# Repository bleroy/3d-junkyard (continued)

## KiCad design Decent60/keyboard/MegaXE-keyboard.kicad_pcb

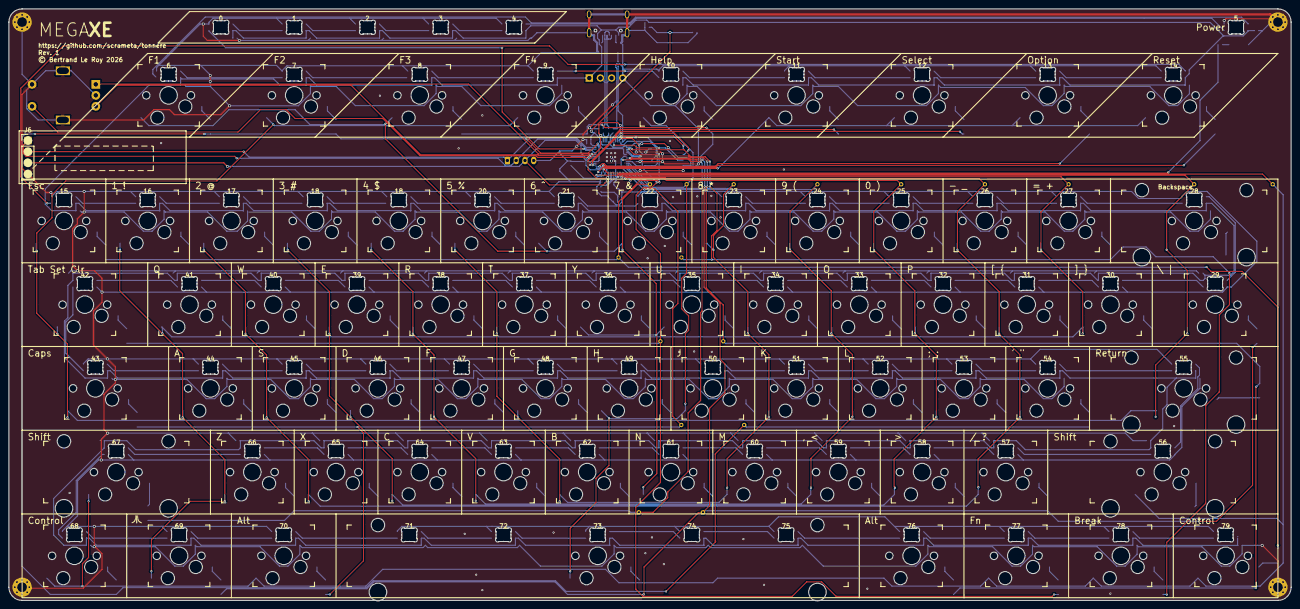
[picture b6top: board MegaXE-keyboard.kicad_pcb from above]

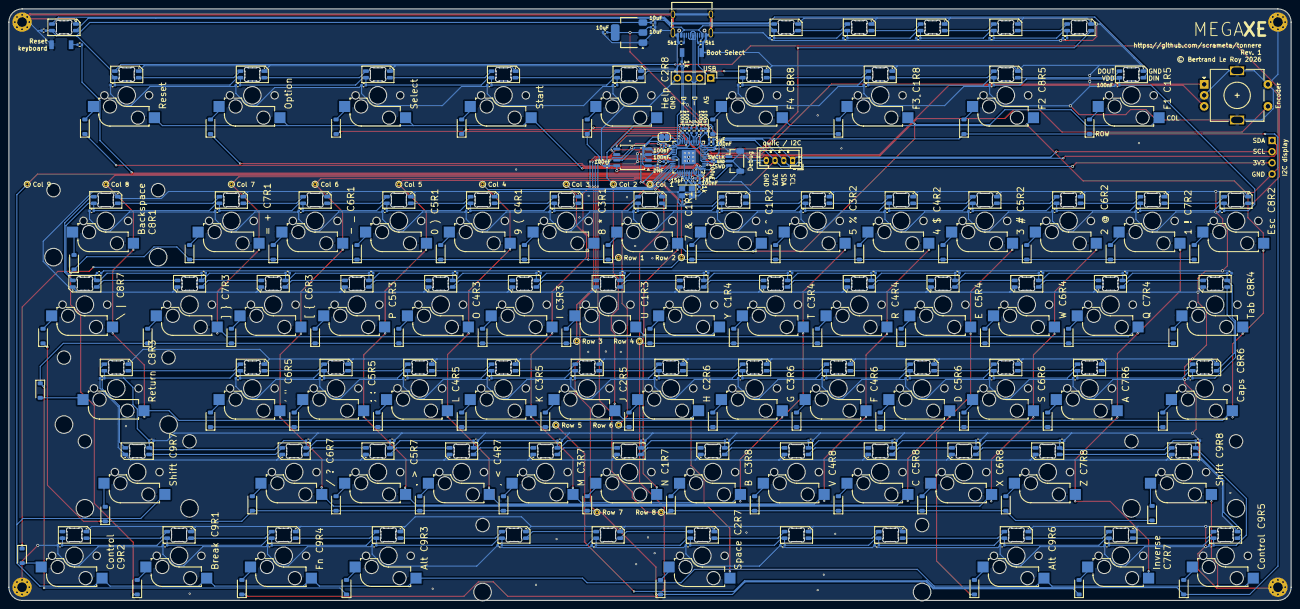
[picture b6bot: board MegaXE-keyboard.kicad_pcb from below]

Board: 2 copper layers, 291.8 x 134.6 mm, 359 parts (288 on the bottom side), 202 nets.

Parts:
C4, C6, C7, C8, C9, C10, C11, C12, C13, C42, C75, C76, C77, C78, C79, C80, C81, C82, C83, C84, C85, C86, C87, C88, C89, C90, C91, C92, C93, C94, C95, C96, C97, C98, C99, C100, C101, C102, C103, C104, C105, C106, C107, C108, C109, C110, C111, C112, C113, C114, C115, C116, C117, C118, C119, C120, C121, C123, C124, C125, C126, C127, C128, C129, C130, C131, C132, C133, C134, C135, C136, C137, C138, C139, C140, C141, C142, C143, C144, C145, C146, C147, C148, C149, C150, C151, C152, C153, C154, C155: 100nF; C_0402_1005Metric
C5, C14: 1uF; C_0402_1005Metric
C24, C25: 15pF; C_0402_1005Metric
C27, C28, C43: 10uF; C_0402_1005Metric
D17, D18, D19, D20, D21, D22, D23, D24, D25, D26, D27, D28, D29, D30, D31, D47, D49, D51, D53, D55, D57, D59, D61, D63, D65, D67, D69, D71, D73, D75, D77, D79, D81, D83, D85, D87, D89, D91, D93, D95, D97, D99, D101, D103, D105, D107, D109, D111, D113, D115, D119, D121, D123, D125, D127, D128, D129, D130, D131, D132, D133, D134, D135, D137, D139, D141, D143, D145, D147, D148: 1N4148W; D_SOD-123
D149, D150, D151, D152, D153, D154, D155, D156, D157, D158, D159, D160, D161, D162, D163, D164, D165, D166, D167, D168, D169, D170, D171, D172, D173, D174, D175, D176, D177, D178, D179, D180, D181, D182, D183, D184, D185, D186, D187, D188, D189, D190, D191, D192, D193, D194, D195, D197, D198, D199, D200, D201, D202, D203, D204, D205, D206, D207, D208, D209, D210, D211, D212, D213, D214, D215, D216, D217, D218, D219, D220, D221, D222, D223, D224, D225, D226, D227, D228, D229: SK6812MINI; LED_SK6812MINI-E_3.2x2.8mm_P1.5mm_ReverseMount
H1, H2, H3, H4: MountingHole_Pad; MountingHole_2.2mm_M2_Pad_Via
J1: Conn_01x04_Socket; JST_PH_B4B-PH-K_1x04_P2.00mm_Vertical
J4: Conn_01x04_Pin; PinHeader_1x04_P2.54mm_Vertical
J5: USB_C_Receptacle_USB2.0_16P; USB_C_Receptacle_C2765186
J6: Conn_01x04; PinHeader_1x04_P2.54mm_Vertical
J9: SM03B-SRSS-TB; JST_SH_BM03B-SRSS-TB_1x03-1MP_P1.00mm_Vertical
R6, R7: 5k1; R_0402_1005Metric
R26, R28: 27; R_0402_1005Metric
R30, R31, R32: 1k; R_0402_1005Metric
R36: DNF; R_0402_1005Metric
R37: 0; SolderJumper-2_P1.3mm_Bridged_RoundedPad1.0x1.5mm
SW1: RotaryEncoder_Switch; RotaryEncoder_Alps_EC11E-Switch_Vertical_H20mm
SW2: SW_BOOT_SELECT; TactileSwitch
SW3: SW_RESET; TactileSwitch
SW10, SW11, SW12, SW13, SW14, SW15, SW16, SW17, SW19, SW20, SW21, SW22, SW23, SW24, SW25, SW26, SW27, SW28, SW29, SW30, SW31, SW32, SW33, SW34, SW35, SW36, SW37, SW38, SW39, SW40, SW41, SW42, SW43, SW44, SW45, SW46, SW47, SW48, SW49, SW50, SW51, SW52, SW53, SW54, SW55, SW56, SW57, SW58, SW59, SW61, SW64, SW65, SW66, SW67, SW68, SW70, SW71, SW72, SW73, SW74, SW76, SW77, SW78, SW79, SW80: MX; Kailh_socket_MX_1-00U
SW18: MX; Kailh_socket_MX_6-25U
SW62, SW63, SW69, SW75: MX; Kailh_socket_MX_2-00U
TP1, TP2, TP3, TP4, TP5, TP6, TP7, TP8, TP9, TP10, TP11, TP12, TP13, TP14, TP15, TP16, TP17: TestPoint; TestPoint_THTPad_D1.0mm_Drill0.5mm
U4: NCP1117-3.3; SOT-223-3_TabPin2
U7: RP2040; QFN-56-1EP_7x7mm_P0.4mm_EP3.2x3.2mm
U9: W25Q128JVS; SOIC-8_5.3x5.3mm_P1.27mm
X1: 12MHz; Crystal_SMD_Abracon_ABM8AIG-4Pin_3.2x2.5mm

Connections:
+1V1: C4.1, C5.1, C6.1, U7.23 (DVDD), U7.45 (VREG_VOUT), U7.50 (DVDD)
+3V3: C7.1, C8.1, C9.1, C10.1, C11.1, C12.1, C13.1, C14.1, C27.1, C28.1, C42.1, J1.3, J6.3, R36.1, U4.2 (VO), U7.1 (IOVDD), U7.10 (IOVDD), U7.22 (IOVDD), U7.33 (IOVDD), U7.42 (IOVDD), U7.43 (ADC_AVDD), U7.44 (VREG_IN), U7.48 (USB_VDD), U7.49 (IOVDD), U9.8 (VCC)
/Controller/FLASH_SS: R36.2, R37.2, U9.1 (~CS)
/Controller/QSPI_SCLK: U7.52 (QSPI_SCLK), U9.6 (CLK)
/Controller/QSPI_SD0: U7.53 (QSPI_SD0), U9.5 (DI(IO0))
/Controller/QSPI_SD1: U7.55 (QSPI_SD1), U9.2 (DO(IO1))
/Controller/QSPI_SD2: U7.54 (QSPI_SD2), U9.3 (IO2)
/Controller/QSPI_SD3: U7.51 (QSPI_SD3), U9.7 (IO3)
/Controller/QSPI_SS: R30.1, R37.1, U7.56 (QSPI_SS)
/Controller/SCL: J1.1, J6.2, U7.41 (GPIO29_ADC3)
/Controller/SDA: J1.2, J6.1, U7.40 (GPIO28_ADC2)
/Controller/SWCLK: J9.1, U7.24 (SWCLK)
/Controller/SWD: J9.3, U7.25 (SWD)
/Controller/USB_D+: J4.3, J5.A6 (D+), J5.B6 (D+), R26.1
/Controller/USB_D-: J4.2, J5.A7 (D-), J5.B7 (D-), R28.1
/Controller/USB_DN: R28.2, U7.46 (USB_DM)
/Controller/USB_DP: R26.2, U7.47 (USB_DP)
/Controller/XIN: C24.1, U7.20 (XIN), X1.1
/Controller/XOUT: R31.2, U7.21 (XOUT)
/Controller/~USB_BOOT: R30.2, SW2.2
/Key0/RGB_IN: D169.4 (DOUT), D178.2 (DIN)
/Key0/RGB_OUT: D178.4 (DOUT), D185.2 (DIN)
/Key1/RGB_IN: D193.2 (DIN), D201.4 (DOUT)
/Key1/RGB_OUT: D186.2 (DIN), D193.4 (DOUT)
/Key2/RGB_OUT: D177.2 (DIN), D186.4 (DOUT)
/Key3/RGB_OUT: D170.2 (DIN), D177.4 (DOUT)
/Key4/RGB_OUT: D167.2 (DIN), D170.4 (DOUT)
/Key5/RGB_OUT: D151.2 (DIN), D167.4 (DOUT)
/Key6/RGB_OUT: D150.2 (DIN), D151.4 (DOUT)
/Key7/RGB_OUT: D150.4 (DOUT), D168.2 (DIN)
/Key8/RGB_OUT: D168.4 (DOUT), D169.2 (DIN)
/KeyA/RGB_IN: D197.2 (DIN), D202.4 (DOUT)
/KeyA/RGB_OUT: D188.2 (DIN), D197.4 (DOUT)
/KeyAlt/RGB_IN: D198.4 (DOUT), D227.2 (DIN)
/KeyAlt/RGB_OUT: D221.2 (DIN), D227.4 (DOUT)
/KeyB/RGB_IN: D155.4 (DOUT), D161.2 (DIN)
/KeyB/RGB_OUT: D161.4 (DOUT), D176.2 (DIN)
/KeyBackslash/RGB_IN: D204.4 (DOUT), D229.2 (DIN)
/KeyBackslash/RGB_OUT: D194.2 (DIN), D229.4 (DOUT)
/KeyBreak/RGB_IN: D210.2 (DIN), D226.4 (DOUT)
/KeyBreak/RGB_OUT: D210.4 (DOUT), D225.2 (DIN)
/KeyC/RGB_IN: D176.4 (DOUT), D184.2 (DIN)
/KeyC/RGB_OUT: D184.4 (DOUT), D187.2 (DIN)
/KeyCaps/RGB_IN: D202.2 (DIN), D206.4 (DOUT)
/KeyComma/RGB_IN: D175.2 (DIN), D179.4 (DOUT)
/KeyComma/RGB_OUT: D162.2 (DIN), D175.4 (DOUT)
/KeyControl/RGB_IN: D205.2 (DIN), D209.4 (DOUT)
/KeyControl/RGB_OUT: D198.2 (DIN), D205.4 (DOUT)
/KeyD/RGB_IN: D181.2 (DIN), D188.4 (DOUT)
/KeyD/RGB_OUT: D174.2 (DIN), D181.4 (DOUT)
/KeyDelete/RGB_IN: D195.4 (DOUT), D204.2 (DIN)
/KeyE/RGB_IN: D172.4 (DOUT), D183.2 (DIN)
/KeyE/RGB_OUT: D183.4 (DOUT), D189.2 (DIN)
/KeyEqual/RGB_IN: D185.4 (DOUT), D195.2 (DIN)
/KeyEsc/RGB_IN: D201.2 (DIN), D211.4 (DOUT)
/KeyF1/RGB_IN: D149.4 (DOUT), D154.2 (DIN)
/KeyF1/RGB_OUT: D154.4 (DOUT), D207.2 (DIN)
/KeyF2/RGB_OUT: D159.2 (DIN), D207.4 (DOUT)
/KeyF3/RGB_OUT: D159.4 (DOUT), D208.2 (DIN)
/KeyF4/RGB_OUT: D160.2 (DIN), D208.4 (DOUT)
/KeyF/RGB_OUT: D163.2 (DIN), D174.4 (DOUT)
/KeyFn/RGB_IN: D226.2 (DIN), D228.4 (DOUT)
/KeyG/RGB_OUT: D157.2 (DIN), D163.4 (DOUT)
/KeyH/RGB_OUT: D156.2 (DIN), D157.4 (DOUT)
/KeyHelp/RGB_OUT: D160.4 (DOUT), D214.2 (DIN)
/KeyI/RGB_IN: D166.2 (DIN), D171.4 (DOUT)
/KeyI/RGB_OUT: D152.2 (DIN), D166.4 (DOUT)
/KeyJ/RGB_OUT: D156.4 (DOUT), D164.2 (DIN)
/KeyK/RGB_OUT: D164.4 (DOUT), D173.2 (DIN)
/KeyL/RGB_OUT: D173.4 (DOUT), D182.2 (DIN)
/KeyLeftBracket/RGB_IN: D190.2 (DIN), D194.4 (DOUT)
/KeyLeftBracket/RGB_OUT: D180.2 (DIN), D190.4 (DOUT)
/KeyLeftShift/RGB_IN: D200.4 (DOUT), D209.2 (DIN)
/KeyM/RGB_OUT: D155.2 (DIN), D162.4 (DOUT)
/KeyO/RGB_IN: D171.2 (DIN), D180.4 (DOUT)
/KeyOption/RGB_IN: D212.2 (DIN), D213.4 (DOUT)
/KeyOption/RGB_OUT: D211.2 (DIN), D212.4 (DOUT)
/KeyPeriod/RGB_IN: D179.2 (DIN), D191.4 (DOUT)
/KeyQ/RGB_IN: D189.4 (DOUT), D199.2 (DIN)
/KeyQ/RGB_OUT: D199.4 (DOUT), D206.2 (DIN)
/KeyQuote/RGB_IN: D182.4 (DOUT), D192.2 (DIN)
/KeyQuote/RGB_OUT: D192.4 (DOUT), D203.2 (DIN)
/KeyR/RGB_IN: D165.4 (DOUT), D172.2 (DIN)
/KeyReturn/RGB_OUT: D203.4 (DOUT), D215.2 (DIN)
/KeyRightAlt/RGB_IN: D224.4 (DOUT), D228.2 (DIN)
/KeyRightShift/RGB_OUT: D191.2 (DIN), D215.4 (DOUT)
/KeySelect/RGB_IN: D213.2 (DIN), D214.4 (DOUT)
/KeySpace/RGB_IN: D158.2 (DIN), D222.4 (DOUT)
/KeySpace/RGB_OUT: D158.4 (DOUT), D223.2 (DIN)
/KeyT/RGB_IN: D153.4 (DOUT), D165.2 (DIN)
/KeyU/RGB_OUT: D152.4 (DOUT), D153.2 (DIN)
/KeyX/RGB_OUT: D187.4 (DOUT), D200.2 (DIN)
/Logo1/RGB_OUT: D216.4 (DOUT), D217.2 (DIN)
/Logo2/RGB_OUT: D217.4 (DOUT), D218.2 (DIN)
/Logo3/RGB_OUT: D218.4 (DOUT), D219.2 (DIN)
/Logo4/RGB_OUT: D219.4 (DOUT), D220.2 (DIN)
/Logo5/RGB_OUT: D149.2 (DIN), D220.4 (DOUT)
/Space1/RGB_OUT: D221.4 (DOUT), D222.2 (DIN)
/Space3/RGB_OUT: D223.4 (DOUT), D224.2 (DIN)
COL_1: SW10.1, SW11.1, SW12.1, SW13.1, SW14.1, SW15.1, SW19.1, TP1.1 (1_1), U7.11 (GPIO8)
COL_2: SW16.1, SW17.1, SW18.1, SW20.1, TP2.1 (1_1), U7.12 (GPIO9)
COL_3: SW21.1, SW22.1, SW23.1, SW24.1, SW25.1, SW26.1, SW27.1, SW28.1, TP3.1 (1_1), U7.13 (GPIO10)
COL_4: SW29.1, SW30.1, SW31.1, SW32.1, SW33.1, SW34.1, SW35.1, SW36.1, TP4.1 (1_1), U7.14 (GPIO11)
COL_5: SW37.1, SW38.1, SW39.1, SW40.1, SW41.1, SW42.1, SW43.1, SW44.1, TP5.1 (1_1), U7.15 (GPIO12)
COL_6: SW45.1, SW46.1, SW47.1, SW48.1, SW49.1, SW50.1, SW51.1, SW52.1, TP6.1 (1_1), U7.16 (GPIO13)
COL_7: SW53.1, SW54.1, SW55.1, SW56.1, SW57.1, SW58.1, SW59.1, TP7.1 (1_1), U7.17 (GPIO14)
COL_8: SW61.1, SW62.1, SW63.1, SW64.1, SW65.1, SW67.1, SW68.1, SW80.1, TP8.1 (1_1), U7.18 (GPIO15)
COL_9: SW66.1, SW69.1, SW70.1, SW75.1, SW76.1, SW77.1, SW78.1, SW79.1, TP9.1 (1_1), U7.27 (GPIO16)
CONSOLE: SW71.1, SW72.1, SW73.1, SW74.1, U7.28 (GPIO17)
EncoderA: SW1.A, U7.37 (GPIO25)
EncoderB: SW1.B, U7.36 (GPIO24)
EncoderSwitch: SW1.S1, U7.35 (GPIO23)
GND: C4.2, C5.2, C6.2, C7.2, C8.2, C9.2, C10.2, C11.2, C12.2, C13.2, C14.2, C24.2, C25.1, C27.2, C28.2, C42.2, C43.1, C75.2, C76.2, C77.2, C78.2, C79.2, C80.2, C81.2, C82.2, C83.2, C84.2, C85.2, C86.2, C87.2, C88.2, C89.2, C90.2, C91.2, C92.2, C93.2, C94.2, C95.2, C96.2, C97.2, C98.2, C99.2, C100.2, C101.2, C102.2, C103.2, C104.2, C105.2, C106.2, C107.2, C108.2, C109.2, C110.2, C111.2, C112.2, C113.2, C114.2, C115.2, C116.2, C117.2, C118.2, C119.2, C120.2, C121.2, C123.2, C124.2, C125.2, C126.2, C127.2, C128.2, C129.2, C130.2, C131.2, C132.2, C133.2, C134.2, C135.2, C136.2, C137.2, C138.2, C139.2, C140.2, C141.2, C142.2, C143.2, C144.2, C145.2, C146.2, C147.2, C148.2, C149.2, C150.2, C151.2, C152.2, C153.2, C154.2, C155.2, D149.1 (VSS), D150.1 (VSS), D151.1 (VSS), D152.1 (VSS), D153.1 (VSS), D154.1 (VSS), D155.1 (VSS), D156.1 (VSS), D157.1 (VSS), D158.1 (VSS), D159.1 (VSS), D160.1 (VSS), D161.1 (VSS), D162.1 (VSS), D163.1 (VSS), D164.1 (VSS), D165.1 (VSS), D166.1 (VSS), D167.1 (VSS), D168.1 (VSS), D169.1 (VSS), D170.1 (VSS), D171.1 (VSS), D172.1 (VSS), D173.1 (VSS), D174.1 (VSS), D175.1 (VSS), D176.1 (VSS), D177.1 (VSS), D178.1 (VSS), D179.1 (VSS), D180.1 (VSS), D181.1 (VSS), D182.1 (VSS), D183.1 (VSS), D184.1 (VSS), D185.1 (VSS), D186.1 (VSS), D187.1 (VSS), D188.1 (VSS), D189.1 (VSS), D190.1 (VSS), D191.1 (VSS), D192.1 (VSS), D193.1 (VSS), D194.1 (VSS), D195.1 (VSS), D197.1 (VSS), D198.1 (VSS), D199.1 (VSS), D200.1 (VSS), D201.1 (VSS), D202.1 (VSS), D203.1 (VSS), D204.1 (VSS), D205.1 (VSS), D206.1 (VSS), D207.1 (VSS), D208.1 (VSS), D209.1 (VSS), D210.1 (VSS), D211.1 (VSS), D212.1 (VSS), D213.1 (VSS), D214.1 (VSS), D215.1 (VSS), D216.1 (VSS), D217.1 (VSS), D218.1 (VSS), D219.1 (VSS), D220.1 (VSS), D221.1 (VSS), D222.1 (VSS), D223.1 (VSS), D224.1 (VSS), D225.1 (VSS), D226.1 (VSS), D227.1 (VSS), D228.1 (VSS), D229.1 (VSS), H1.1 (1_1), H2.1 (1_1), H3.1 (1_1), H4.1 (1_1), J1.4, J4.4, J5.A1 (GND), J5.A12 (GND), J5.B1 (GND), J5.B12 (GND), J5.S1 (SHIELD), J6.4, J9.2, J9.MP (MountPin), R6.2, R7.2, SW1.C, SW1.MP, SW1.S2, SW2.1, SW3.1, U4.1 (GND), U7.19 (TESTEN), U7.57 (GND), U9.4 (GND), X1.2, X1.4
unnamed: C25.2, R31.1, X1.3
unnamed: D17.2 (A), SW10.2
unnamed: D18.2 (A), SW11.2
unnamed: D19.2 (A), SW12.2
unnamed: D20.2 (A), SW13.2
unnamed: D21.2 (A), SW14.2
unnamed: D22.2 (A), SW15.2
unnamed: D23.2 (A), SW16.2
unnamed: D24.2 (A), SW17.2
unnamed: D25.2 (A), SW18.2
unnamed: D26.2 (A), SW19.2
unnamed: D27.2 (A), SW20.2
unnamed: D28.2 (A), SW21.2
unnamed: D29.2 (A), SW22.2
unnamed: D30.2 (A), SW23.2
unnamed: D31.2 (A), SW24.2
unnamed: D47.2 (A), SW25.2
unnamed: D49.2 (A), SW26.2
unnamed: D51.2 (A), SW27.2
unnamed: D53.2 (A), SW28.2
unnamed: D55.2 (A), SW29.2
unnamed: D57.2 (A), SW30.2
unnamed: D59.2 (A), SW31.2
unnamed: D61.2 (A), SW32.2
unnamed: D63.2 (A), SW33.2
unnamed: D65.2 (A), SW34.2
unnamed: D67.2 (A), SW35.2
unnamed: D69.2 (A), SW36.2
unnamed: D71.2 (A), SW37.2
unnamed: D73.2 (A), SW38.2
unnamed: D75.2 (A), SW39.2
unnamed: D77.2 (A), SW40.2
unnamed: D79.2 (A), SW41.2
unnamed: D81.2 (A), SW42.2
unnamed: D83.2 (A), SW43.2
unnamed: D85.2 (A), SW44.2
unnamed: D87.2 (A), SW45.2
unnamed: D89.2 (A), SW46.2
unnamed: D91.2 (A), SW47.2
unnamed: D93.2 (A), SW48.2
unnamed: D95.2 (A), SW49.2
unnamed: D97.2 (A), SW50.2
unnamed: D99.2 (A), SW51.2
unnamed: D101.2 (A), SW52.2
unnamed: D103.2 (A), SW53.2
unnamed: D105.2 (A), SW54.2
unnamed: D107.2 (A), SW55.2
unnamed: D109.2 (A), SW56.2
unnamed: D111.2 (A), SW57.2
unnamed: D113.2 (A), SW58.2
unnamed: D115.2 (A), SW59.2
unnamed: D119.2 (A), SW61.2
unnamed: D121.2 (A), SW62.2
unnamed: D123.2 (A), SW63.2
unnamed: D125.2 (A), SW64.2
unnamed: D127.2 (A), SW65.2
unnamed: D128.2 (A), SW80.2
unnamed: D129.2 (A), SW66.2
unnamed: D130.2 (A), SW76.2
unnamed: D131.2 (A), SW67.2
unnamed: D132.2 (A), SW78.2
unnamed: D133.2 (A), SW68.2
unnamed: D134.2 (A), SW79.2
unnamed: D135.2 (A), SW69.2
unnamed: D137.2 (A), SW70.2
unnamed: D139.2 (A), SW71.2
unnamed: D141.2 (A), SW72.2
unnamed: D143.2 (A), SW73.2
unnamed: D145.2 (A), SW74.2
unnamed: D147.2 (A), SW75.2
unnamed: D148.2 (A), SW77.2
unnamed: J5.A5 (CC1), R7.1
unnamed: J5.B5 (CC2), R6.1
unnamed: R32.2, SW3.2
unnamed: R32.1, U7.26 (RUN)
OPTION: D141.1 (K), U7.30 (GPIO19)
RESET: D139.1 (K), U7.29 (GPIO18)
RGB: D216.2 (DIN), U7.38 (GPIO26_ADC0)
ROW_1: D17.1 (K), D53.1 (K), D55.1 (K), D71.1 (K), D89.1 (K), D103.1 (K), D123.1 (K), D137.1 (K), TP10.1 (1_1), U7.2 (GPIO0)
ROW_2: D18.1 (K), D51.1 (K), D57.1 (K), D73.1 (K), D87.1 (K), D105.1 (K), D119.1 (K), D130.1 (K), TP11.1 (1_1), U7.3 (GPIO1)
ROW_3: D19.1 (K), D49.1 (K), D59.1 (K), D75.1 (K), D93.1 (K), D113.1 (K), D121.1 (K), D134.1 (K), TP12.1 (1_1), U7.4 (GPIO2)
ROW_4: D20.1 (K), D47.1 (K), D61.1 (K), D77.1 (K), D99.1 (K), D111.1 (K), D131.1 (K), D148.1 (K), TP13.1 (1_1), U7.5 (GPIO3)
ROW_5: D21.1 (K), D23.1 (K), D31.1 (K), D63.1 (K), D79.1 (K), D97.1 (K), D125.1 (K), D129.1 (K), TP14.1 (1_1), U7.6 (GPIO4)
ROW_6: D24.1 (K), D30.1 (K), D65.1 (K), D81.1 (K), D95.1 (K), D109.1 (K), D127.1 (K), D132.1 (K), TP15.1 (1_1), U7.7 (GPIO5)
ROW_7: D22.1 (K), D25.1 (K), D29.1 (K), D67.1 (K), D83.1 (K), D91.1 (K), D115.1 (K), D128.1 (K), D147.1 (K), TP16.1 (1_1), U7.8 (GPIO6)
ROW_8: D26.1 (K), D27.1 (K), D28.1 (K), D69.1 (K), D85.1 (K), D101.1 (K), D107.1 (K), D133.1 (K), D135.1 (K), TP17.1 (1_1), U7.9 (GPIO7)
SELECT: D143.1 (K), U7.31 (GPIO20)
START: D145.1 (K), U7.32 (GPIO21)
VSYS: C43.2, C75.1, C76.1, C77.1, C78.1, C79.1, C80.1, C81.1, C82.1, C83.1, C84.1, C85.1, C86.1, C87.1, C88.1, C89.1, C90.1, C91.1, C92.1, C93.1, C94.1, C95.1, C96.1, C97.1, C98.1, C99.1, C100.1, C101.1, C102.1, C103.1, C104.1, C105.1, C106.1, C107.1, C108.1, C109.1, C110.1, C111.1, C112.1, C113.1, C114.1, C115.1, C116.1, C117.1, C118.1, C119.1, C120.1, C121.1, C123.1, C124.1, C125.1, C126.1, C127.1, C128.1, C129.1, C130.1, C131.1, C132.1, C133.1, C134.1, C135.1, C136.1, C137.1, C138.1, C139.1, C140.1, C141.1, C142.1, C143.1, C144.1, C145.1, C146.1, C147.1, C148.1, C149.1, C150.1, C151.1, C152.1, C153.1, C154.1, C155.1, D149.3 (VDD), D150.3 (VDD), D151.3 (VDD), D152.3 (VDD), D153.3 (VDD), D154.3 (VDD), D155.3 (VDD), D156.3 (VDD), D157.3 (VDD), D158.3 (VDD), D159.3 (VDD), D160.3 (VDD), D161.3 (VDD), D162.3 (VDD), D163.3 (VDD), D164.3 (VDD), D165.3 (VDD), D166.3 (VDD), D167.3 (VDD), D168.3 (VDD), D169.3 (VDD), D170.3 (VDD), D171.3 (VDD), D172.3 (VDD), D173.3 (VDD), D174.3 (VDD), D175.3 (VDD), D176.3 (VDD), D177.3 (VDD), D178.3 (VDD), D179.3 (VDD), D180.3 (VDD), D181.3 (VDD), D182.3 (VDD), D183.3 (VDD), D184.3 (VDD), D185.3 (VDD), D186.3 (VDD), D187.3 (VDD), D188.3 (VDD), D189.3 (VDD), D190.3 (VDD), D191.3 (VDD), D192.3 (VDD), D193.3 (VDD), D194.3 (VDD), D195.3 (VDD), D197.3 (VDD), D198.3 (VDD), D199.3 (VDD), D200.3 (VDD), D201.3 (VDD), D202.3 (VDD), D203.3 (VDD), D204.3 (VDD), D205.3 (VDD), D206.3 (VDD), D207.3 (VDD), D208.3 (VDD), D209.3 (VDD), D210.3 (VDD), D211.3 (VDD), D212.3 (VDD), D213.3 (VDD), D214.3 (VDD), D215.3 (VDD), D216.3 (VDD), D217.3 (VDD), D218.3 (VDD), D219.3 (VDD), D220.3 (VDD), D221.3 (VDD), D222.3 (VDD), D223.3 (VDD), D224.3 (VDD), D225.3 (VDD), D226.3 (VDD), D227.3 (VDD), D228.3 (VDD), D229.3 (VDD), J4.1, J5.A4 (VBUS), J5.A9 (VBUS), J5.B4 (VBUS), J5.B9 (VBUS), U4.3 (VI)

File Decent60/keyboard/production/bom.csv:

Designator,Footprint,Quantity,Value,LCSC Part #
"C10, C100, C101, C102, C103, C104, C105, C106, C107, C108, C109, C11, C110, C111, C112, C113, C114, C115, C116, C117, C118, C119, C12, C120, C121, C123, C124, C125, C126, C127, C128, C129, C13, C130, C131, C132, C133, C134, C135, C136, C137, C138, C139, C140, C141, C142, C143, C144, C145, C146, C147, C148, C149, C150, C151, C152, C153, C154, C155, C4, C42, C6, C7, C75, C76, C77, C78, C79, C8, C80, C81, C82, C83, C84, C85, C86, C87, C88, C89, C9, C90, C91, C92, C93, C94, C95, C96, C97, C98, C99",0402,90,100nF,C1525
"C14, C5",0402,2,1uF,C52923
"C24, C25",0402,2,15pF,C1548
"C27, C28, C43",0402,3,10uF,C15525
"D101, D103, D105, D107, D109, D111, D113, D115, D119, D121, D123, D125, D127, D128, D129, D130, D131, D132, D133, D134, D135, D137, D139, D141, D143, D145, D147, D148, D17, D18, D19, D20, D21, D22, D23, D24, D25, D26, D27, D28, D29, D30, D31, D47, D49, D51, D53, D55, D57, D59, D61, D63, D65, D67, D69, D71, D73, D75, D77, D79, D81, D83, D85, D87, D89, D91, D93, D95, D97, D99",D_SOD-123,70,1N4148W,C81598
"D149, D150, D151, D152, D153, D154, D155, D156, D157, D158, D159, D160, D161, D162, D163, D164, D165, D166, D167, D168, D169, D170, D171, D172, D173, D174, D175, D176, D177, D178, D179, D180, D181, D182, D183, D184, D185, D186, D187, D188, D189, D190, D191, D192, D193, D194, D195, D197, D198, D199, D200, D201, D202, D203, D204, D205, D206, D207, D208, D209, D210, D211, D212, D213, D214, D215, D216, D217, D218, D219, D220, D221, D222, D223, D224, D225, D226, D227, D228, D229",LED_SK6812MINI-E_3.2x2.8mm_P1.5mm_ReverseMount,80,SK6812MINI,C5378731
J5,USB_C_Receptacle_C2765186,1,USB_C_Receptacle_USB2.0_16P,C2765186
"R26, R28",0402,2,27,C138021
"R30, R31, R32",0402,3,1k,C11702
"R6, R7",0402,2,5k1,C25905
"SW10, SW11, SW12, SW13, SW14, SW15, SW16, SW17, SW19, SW20, SW21, SW22, SW23, SW24, SW25, SW26, SW27, SW28, SW29, SW30, SW31, SW32, SW33, SW34, SW35, SW36, SW37, SW38, SW39, SW40, SW41, SW42, SW43, SW44, SW45, SW46, SW47, SW48, SW49, SW50, SW51, SW52, SW53, SW54, SW55, SW56, SW57, SW58, SW59, SW61, SW64, SW65, SW66, SW67, SW68, SW70, SW71, SW72, SW73, SW74, SW76, SW77, SW78, SW79, SW80",Kailh_socket_MX_1-00U,65,MX,C41430893
SW18,Kailh_socket_MX_6-25U,1,MX,C41430893
SW2,TactileSwitch,1,SW_BOOT_SELECT,C720477
SW3,TactileSwitch,1,SW_RESET,C720477
"SW62, SW63, SW69, SW75",Kailh_socket_MX_2-00U,4,MX,C41430893
U4,SOT-223-3_TabPin2,1,NCP1117-3.3,C6186
U7,QFN-56-1EP_7x7mm_P0.4mm_EP3.2x3.2mm,1,RP2040,C2040
U9,SOIC-8_5.3x5.3mm_P1.27mm,1,W25Q128JVS,C97521
X1,Crystal_SMD_Abracon_ABM8AIG-4Pin_3.2x2.5mm,1,12MHz,C9002

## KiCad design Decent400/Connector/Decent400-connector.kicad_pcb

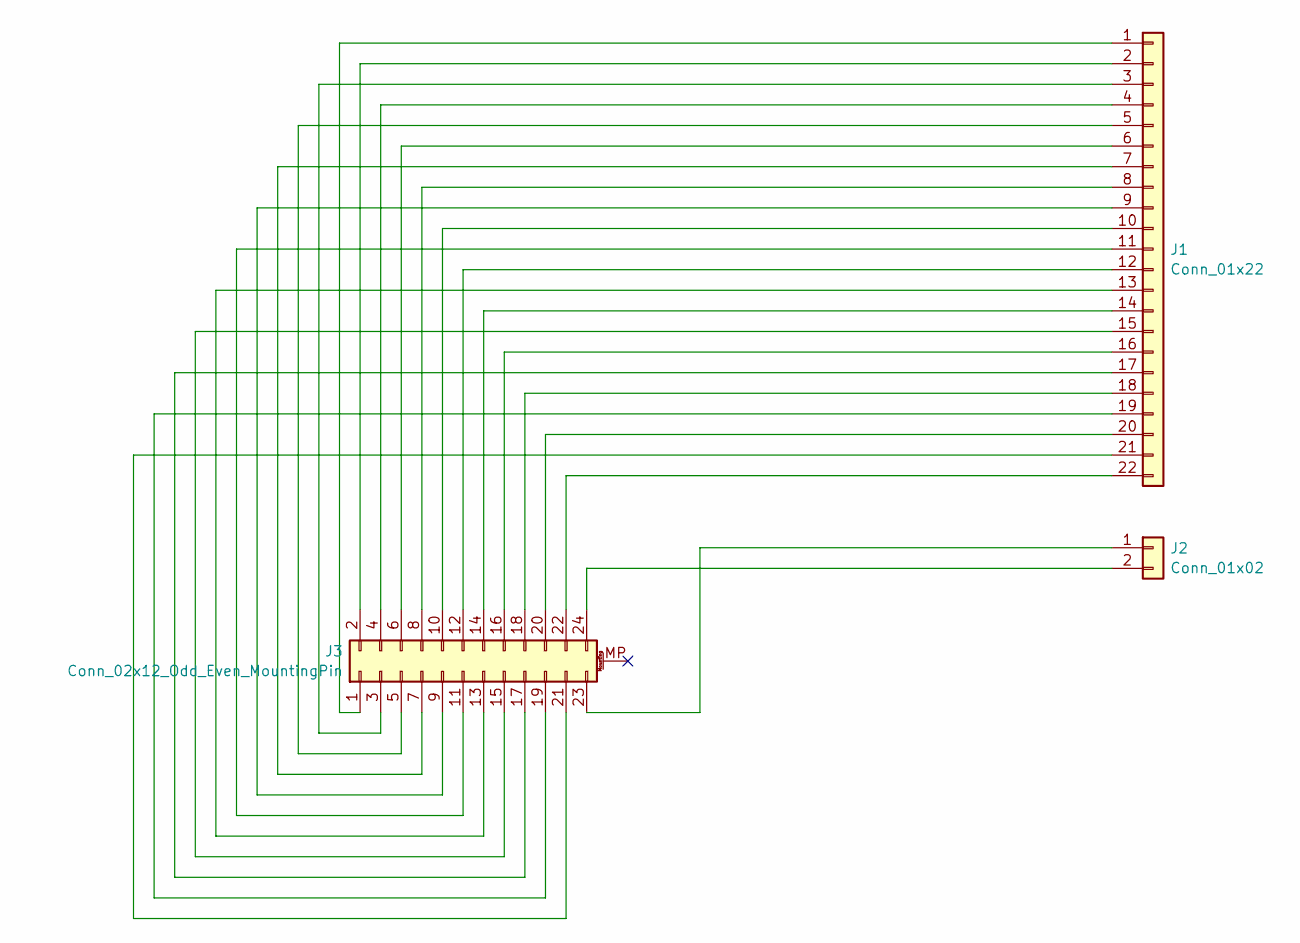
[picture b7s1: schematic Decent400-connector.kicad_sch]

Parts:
J1: Conn_01x22; PinHeader_1x22_P2.54mm_Vertical
J2: Conn_01x02; PinHeader_1x02_P2.54mm_Vertical
J3: Conn_02x12_Odd_Even_MountingPin; IDC-Header_2x12_P2.54mm_Vertical

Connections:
unnamed: J1.1, J3.1
unnamed: J1.2, J3.2
unnamed: J1.3, J3.3
unnamed: J1.4, J3.4
unnamed: J1.5, J3.5
unnamed: J1.6, J3.6
unnamed: J1.7, J3.7
unnamed: J1.8, J3.8
unnamed: J1.9, J3.9
unnamed: J1.10, J3.10
unnamed: J1.11, J3.11
unnamed: J1.12, J3.12
unnamed: J1.13, J3.13
unnamed: J1.14, J3.14
unnamed: J1.15, J3.15
unnamed: J1.16, J3.16
unnamed: J1.17, J3.17
unnamed: J1.18, J3.18
unnamed: J1.19, J3.19
unnamed: J1.20, J3.20
unnamed: J1.21, J3.21
unnamed: J1.22, J3.22
unnamed: J2.1, J3.23
unnamed: J2.2, J3.24

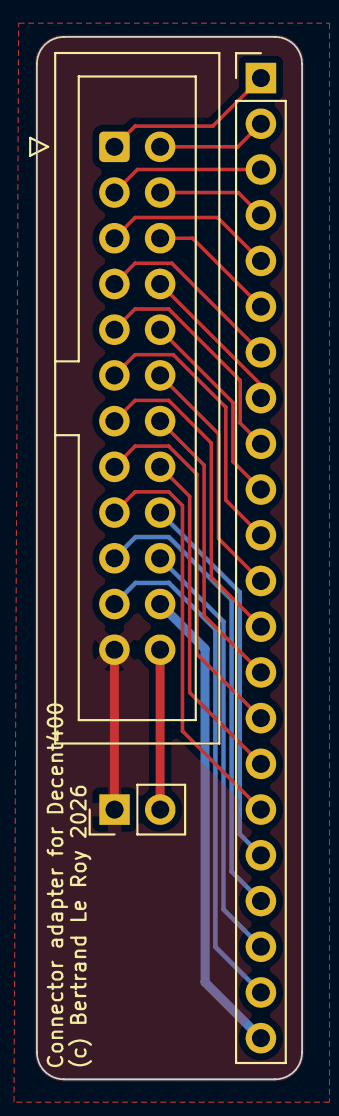
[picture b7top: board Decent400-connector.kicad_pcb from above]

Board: 2 copper layers, 14.7 x 57.9 mm, 3 parts (0 on the bottom side), 24 nets.

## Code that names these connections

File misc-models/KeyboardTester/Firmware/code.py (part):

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    return ios[pin]

# Setup the display
# VCC is just GPIO16 set to high and GND is GPIO17 set to low.
OLED_WIDTH = 128
OLED_HEIGHT = 32
OLED_SDA = board.GP28
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        self.col_pins = []
        self.matrix = []
        self.charmap = dict()
        self.console_pin = None
        self.console = None
        self.start_pin = None
        self.start = None
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        self.select_pin = None
        self.select = None
        self.select_key = 'Select'
        self.option_pin = None
        self.option = None
        self.option_key = 'Option'
        self.reset_pin = None
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            pinio = get_io(pin)
            pinio.direction = digitalio.Direction.INPUT
            pinio.pull = digitalio.Pull.UP
        # Setup the console GND pin
        if self.console_pin != None:
            self.console = get_io(self.console_pin)
            self.console.direction = digitalio.Direction.OUTPUT
            self.console.value = False
        # Setup the START pin
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            self.select.direction = digitalio.Direction.INPUT
            self.select.pull = digitalio.Pull.UP
            pixels[coordinates[self.select_key][2]] = modulate(ORANGE, led_intensity)
        # Setup the OPTION pin
        if self.option_pin != None:
            self.option = get_io(self.option_pin)
            self.option.direction = digitalio.Direction.INPUT
            self.option.pull = digitalio.Pull.UP
            pixels[coordinates[self.option_key][2]] = modulate(ORANGE, led_intensity)
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            [None, 'H',     'G',  'F',  'D',  'S',    'A',       'RightControl', None],
            ['N',  'Space', 'M',  ',<', '.>', '/?',   'Inverse', None,           None],
            ['F3', 'F8',    'B',  'V',  'C',  'X',    'Z',       'F4',           'LeftShift']]
        self.console_pin = board.GP4
        self.start_pin = board.GP22
        self.start_key = 'F9'
        self.select_pin = board.GP23
        self.select_key = 'F10'
        self.option_pin = board.GP24
        self.option_key = 'F11'
        self.reset_pin = board.GP25
        self.reset_key = 'F12'
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            [None, 'H',     'G',  'F',  'D',  'S',    'A',       'RightControl', None],
            ['N',  'Space', 'M',  ',<', '.>', '/?',   'Inverse', None,           None],
            ['F3', 'Help',  'B',  'V',  'C',  'X',    'Z',       'F4',           'LeftShift']]
        self.console_pin = board.GP19
        self.start_pin = board.GP21
        self.start_key = 'Start'
        self.select_pin = board.GP22
        self.select_key = 'Select'
        self.option_pin = board.GP23
        self.option_key = 'Option'
        self.reset_pin = board.GP24
        self.reset_key = 'Reset'
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            [None, 'H',     'G',  'F',  'D',  'S',    'A',       'RightControl', None],
            ['N',  'Space', 'M',  ',<', '.>', '/?',   'Inverse', None,           None],
            [None, None,    'B',  'V',  'C',  'X',    'Z',       None,           'LeftShift']]
        self.console_pin = board.GP23
        self.start_pin = board.GP22
        self.start_key = 'Start'
        self.select_pin = board.GP21
        self.select_key = 'Select'
        self.option_pin = board.GP20
        self.option_key = 'Option'
        self.reset_pin = board.GP19
        self.reset_key = 'Reset'
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            ['N',  'Space', 'M',  ',<', '.>', '/?',   'F11',     None,           None],
            ['F7', 'F10',   'B',  'V',  'C',  'X',    'Z',       'F8',           'LeftShift']]
        self.power_pin = board.GP2
        self.console_pin = board.GP3
        self.start_pin = board.GP6
        self.start_key = 'F2'
        self.select_pin = board.GP5
        self.select_key = 'F3'
        self.option_pin = board.GP4
        self.option_key = 'F4'
        self.reset_pin = board.GP7
        self.reset_key = 'Esc'
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
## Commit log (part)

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2023-10-24 Fix broken console key link in readme.
2023-10-24 Probe holder STL
2023-10-24 Decent1200 console keys + stickers
2023-11-06 Decent800 PCB
2023-11-07 Decent800 PCB finalized
2023-11-11 Decent800 plate
2023-11-11 Rail adjustments
2023-11-15 Decent400 initial work
2023-11-15 Decent800 logo
2023-11-16 Finalizing Decent400 PCB
2023-11-21 XL adapters
2023-11-21 Decent800 WIP
2023-11-22 Finalize Decent800 PCB and plate
2023-11-22 Finalize Decent400 PCB and plate
2023-11-23 Decent400 & 800 production files, dir cleanups
2023-11-23 Move the 1200 library
2023-11-29 Update DecentXL readme
2023-12-04 Small XL bracket adjustment for 600XL pillar clearance
2023-12-05 Decent400 caps
2023-12-09 Decent800 rev. 2
2023-12-11 Finish circle drawing algorithms test page
2023-12-11 1200XL badge replacement
2023-12-19 Decent 1200 rev 3 WIP
2023-12-20 Decent1200 Rev. 3 WIP
2023-12-21 Finish Decent1200 PCB Rev. 3
2023-12-21 Decent1200 Rev. 3 Production files
2023-12-29 Hex Lattice project prototype
2023-12-29 Catchup with local
2024-01-03 Decent 400 Rev. 2
2024-01-03 DecentXL Rev. 4 WIP
2024-01-03 Finished circle for Atari
2024-01-05 DecentXL Plate rev.4m
2024-01-05 Alps and Stackpole adapters
2024-01-12 Update readme.md after Jan Beta's video
2024-01-14 DecentXL Rev 4 vintage WIP
2024-01-14 Fix inv key on Decent1200
    3D printed parts for 1200
2024-01-14 Decent1200 inv key fixes in schematic and PCB
2024-01-20 DecentXL Rev. 4v
2024-01-20 Hex lattice firmware and enclosure
2024-01-20 XL Console key height
    Alps stabilizer insert, first rev.
2024-01-29 DecentXL rev. 4.1m and rev. 4v
2024-01-31 XL bracket adjustments.
2024-02-19 Decent400W wide version of the 400 keyboard
2024-02-19 DecentXL Rev. 4 with separate vintage and modern versions
2024-02-19 DecentXL Modern cut trace fix
2024-02-19 DecentXL Vintage issues fixed
2024-02-20 Update DecentXL documentation
    Create new STLs for console keys
2024-02-22 Decent 1200 readme
    DecentXL readme changes
2024-03-21 Microscope arm work
2024-03-21 Minor hex lattice change
2024-03-21 DecentXL modern revision
2024-03-21 Minor Decent1200 change
2024-03-27 Decent400 enclosure and USB firmware
2024-03-27 Update the WASD template for 400 caps
2024-03-29 Decent400 enclosure fix to leave more room to the USB cable
    Updated USB firmware
2024-04-06 Improved XE console key plates
    New 9-key console plate
2024-04-07 DecentXL bracket fixes & console key plate
    The console key plate is now strictly necessary but a nice to have
2024-04-08 XL right bracket oopsie
2024-04-15 Internal Decent400 WIP
2024-04-16 1200 console keys and keyboard support updates
2024-04-16 Decent 400i routed
2024-04-17 Rename prod files for Decent400i
2024-04-28 Add an Altirra mapping file for DecentXE
2024-05-07 DecentKL WIP
2024-05-10 DecenTKL ready for prod
2024-05-12 Decent1200 Rev. 4m
    Modern-only version of the Decent1200 keyboard
2024-05-15 Updated 400 cap set preview
2024-06-30 Decent800 brackets
2024-06-30 Some version catch-up, and 800 readme
2024-07-21 Misc models
2024-07-21 DecenTKL 3D models
2024-07-21 DecenTKL WIP
    Enclosure
    PCB adjustments
    Firmware prototype
2024-07-21 Git ignore update
2024-07-21 DecentXE files moved from the Atari130MX directory to DecentXE
    DecentXE updated to rev. 15
2024-07-22 Add DecentUSB readme
    Reorganize directories
2024-07-29 Decent 800 Rev 2.1
2024-07-29 Finish DecenTKL enclosure
2024-07-29 Small DecentXE project change
2024-07-29 DecentUSB Readme
2024-07-30 DecentUSB rev 1.1 cut
2024-08-09 DecenTKL updates
    # Conflicts:
    # DecenTKL/Caps/ConsoleXE-F1-4.FCStd
    # DecenTKL/Enclosure/DecenTKL-Enclosure.FCStd
2024-08-12 DecenTKL numpad
2024-08-12 Minor DecentXL changes
2024-08-12 Chip breakout boards use larger holes to allow for precision sockets to go through
2024-08-12 Minor Decent USB adapter changes
2024-08-19 DecenTKL numpad update
2024-08-19 Change pcb interconnect on vintage board
    This replaces the discontinued Molex interconnect at J2 with
    a current, and significantly less expensive, Amphenol part.
    Minor trace routing and nearby part placement adjustments
    made as necessary to accommodate the new footprint.
2024-08-19 Replace author info silks
2024-08-24 Finalizing the enclosures rev 1 for DecenTKL
2024-08-25 DecenTKL NumPad WIP
2024-08-25 Hex RGB matrix updades
2024-08-26 Add rubber feet footprint for DecenTKL numpad enclosure
2024-08-26 Fix on the DecenTKL numpad enclosure proto
2024-09-04 Guitar pedal rack
    Misc models cleanup
    Fixes to hex lattice 3D model
2024-09-04 Fixed production orientation of one of the RGB LEDs
2024-09-07 Fix D36 orientation in DecnTKL NumPad
2024-09-12 DecentUSB Host rev. 2 schematic done
    RS2350 instead of Pi Pico
    ESP32 for WiFi
    4-ports USB hub
    Full support for 2 joysticks
    Level shifting on all lines
    2 RGB LEDs + 1 single color LED
2024-09-13 DecentUSB Host adjustments
    Internal RGB LED is now a neopixel
    Added port for additional neopixels chained behind the on-board one
    Added an expansion port for the leftover GPIOs and the OLED display
    Added power source selection MOSFET
2024-09-20 DecentUSB Host board rev. 2
2024-09-29 DecenTKL enclosure and numpad WIP
2024-09-29 DecentCart 2040 rev 1.1
    Also, schematic for DecentCart 2350
2024-09-30 DecentCart 2040 enclosure
2024-10-01 DecentCart2040 adjustments
2024-10-02 More DecentCart2040 adjustments
2024-10-05 Update the 400 keyboard's USB firmware to support The400 Mini key codes for Atari/Inv, Help and F1-4
2024-10-08 Hex lattice firmware update
2024-10-08 Decent1200 rev. 5m
2024-10-11 VertiCart vertical cartridge adapter for XE computers
2024-10-14 DecentCart2040 enclosure
2024-10-14 DecenTKL NumPad enclosure and F keys
2024-10-15 DecentCart 2040 rev. 1.1 fixes
2024-10-19 DecentCart2040 rev. 1.1
2024-10-19 Improve 400 cart port
2024-10-19 Improve XL and XEGS cart port, rename the models
2024-10-20 WIP on 1200XL cart port
2024-10-20 1200XL cart port breakout and adapter board with BOM
2024-10-20 Small changes on the 1200XL cart port
2024-10-20 Small BOM and model adjustments
2024-10-24 VertiCart base enclosure / support
2024-10-24 Minishelf updates
2024-11-11 VertiCart
2024-11-11 Updated DecentXL BOM
2024-11-11 DecenTKL enclosure update
2024-11-13 DecentUSB Host 2040 rev. 3
    Now using the already available RP2040 MCU
2024-11-14 Small production adjustment to DecentUSB 2040
2024-11-14 Some DecenTKL printed parts adjustments
2024-11-30 DecentXL stackpole vintage adapters fix
2024-11-30 DecentXL stbilizer vintage adapter adjustment
2024-12-02 Toothbrush charging base
2025-01-05 Atari 5200 AV port
2025-01-10 DecentCart 2350 component placement
2025-01-10 Decent800 adjustments
2025-01-10 DecentXL adjustments
2025-01-10 Atari 5200 AV port adjustments
2025-01-10 Cello case repair part
2025-01-10 LED bass guitar strap
2025-01-10 Nano PC sample images
2025-01-11 Update XL, XE and 1200 readmes for new GoblinTech key cap templates
2025-01-11 XL PBI breakout
2025-01-12 DecenttCart 2350 routed
2025-01-17 Atari 5200 S-video board
    Adapted from low_budget's design
2025-01-17 Atari S-video mod prototype
2025-01-26 DecentCart5200
    PCB rev. 2 and enclosure
    Atari 5200 edge connector footprint
    plus Alps EC21 rotary encoder
2025-01-26 Small DecentCart2040 and 2350 changes
2025-01-26 Small chipshift changes
2025-02-05 Darker brown for the XL key cap template
2025-02-10 Arrietty's hair clip
2025-02-17 Less Y in XE Falcon cap template.
2025-03-02 Project updates
2025-03-02 Doll keyboard model
2025-03-02 Decent keyboard tester
2025-03-02 DecentCart 5200 WIP
2025-03-02 XE console cap stickers
2025-03-06 Keyboard tester supports USB keyboards
2025-03-07 Add Atari XE mode to keyboard tester
2025-03-07 Fix bug where you can't cycle modes all the way
2025-03-08 Cleanup, add support for XL keyboards
2025-03-08 Add output of the pressed key
2025-03-09 Better handle F keys
2025-03-10 How to sell Decent keyboards
2025-03-10 minor changes to the seller doc
2025-03-16 DecentCart5200 rev.2
2025-03-17 Finalize DecentCart 2350 rev.2
2025-03-17 DecentXE switch soldering mask
2025-04-11 Bouton grille pains
2025-04-11 WIP support for XL and XE keyboards
2025-04-12 Better mapping of XL and XE keys, color currently pressed key white
2025-04-13 Atari 800 keyboard support in the tester
2025-04-13 Atari 400 keyboard support in tester
2025-04-16 Retro Keyboard Tester support for 1200XL
    Fixes to the Decent1200 keyboard schematic
2025-04-16 Decent Retro Keyboard Tester readme
2025-04-16 Small readme fixes
2025-04-16 Fix 800 BOM
2025-05-28 Simple can models
2025-05-28 Parametric peg board and accessories
2025-05-29 Update docs for 800M
2025-07-22 Fix BOM and position links from seller docs
2025-07-30 Fix R switch position on the 1200 keyboard
2025-08-22 WIP DecentUSB 2350B
2025-08-22 Misc models: catadioptre
2025-08-22 DecentCart WIP
2025-10-12 More diodes out of the way of stabilizers
    Return and delete
2025-10-12 Update DecentXE rendering
2025-10-29 DecentCart2354B
    Rev. 3 of DecentCart
2025-11-22 Decent 400 3i
    Low-profile version
    Caps to follow
2025-11-23 Decent 400 tweaks
    Removed unnecessary diodes
    Cleaned up production files
2025-11-23 DecentCart production file refresh
2025-12-02 Add a plate for the low-profile 400 keyboard
2025-12-02 Minor visibility updates
2026-01-06 New parametric FreeCad model for vintage stems
2026-01-06 Ignore prl files
2026-01-14 Fix a small alignment error on console keys
2026-01-31 Add brackets to XL BOM in builder's doc
2026-02-02 DecentXE rev 16
    [x] Power LED switched to red in BOM
    [x] Optional red LED diffuser 3D model
    [x] Mid-keyboard support 3D model
    [x] Back of the board padding 3D model for better fit in the XE case
    [x] Console keys have stabilization holes in PCB and plate
    [x] Plate covers the whole width of the keyboard and conoles keys area
2026-02-02 Cable rev. 2
    Longer contacts on the Atari side
2026-02-02 Remove old file
2026-02-02 Update docs
2026-02-03 Add photo of XE rev 15 padding
2026-02-03 img size
2026-02-04 ThockFactory XE Falcon key cap set
2026-02-09 Bambu H2C vertical exhaust
2026-02-09 Console key remodel in FreeCAD
2026-02-09 GridFinity thread spool trays
2026-02-09 Update cable rendering picture
2026-02-10 Fabrication tweaks for DecentXE
2026-02-10 Add fabrication comment to flex cable
2026-02-22 DecentXE rev 16.1 Modern
    Moved the cable slot and connector apart for easier assembly.
    Rerouted the whole thing with wider power tracks.
2026-02-22 Update documentation to point to the new XE 16.1 Modern files
2026-03-01 Unimportant tweaks
2026-03-01 1200 overlay for keyboard tester
2026-03-01 A simple parametric foot thingy I needed
2026-03-04 Thockfactory files fix
2026-03-14 The Gridfinity soldering workbench
2026-03-14 Add photo of DecenTKL
2026-03-17 Decent400 rev 4.2i
    Moved the luminosity pot left of the right shift key so it's still accessible but not normally visible
    Changed the connector to an IDC connector between the main part of the keyboard and the console keys
    Fixed alignment issues on console keys
    Created all-new cap legends, fake test caps and printed rigs for UV home printing
2026-03-22 Decent400 rev 4.2m
2026-03-28 Parametric models for OEM profile key caps
2026-03-28 Gridfinity electronics workbench
2026-03-28 Low profile 400 cap printing
2026-03-28 XE accessories moved to 3mf from stl
2026-03-30 More cap work
2026-03-30 Add rig to print on the side of MX caps
2026-04-02 Wider opening on front print rigs
2026-04-04 Some random models
2026-04-06 Small adjustment to the position of console keys for the DecentXE keyboard
2026-04-07 Decent400 rev 4.3i
    Change the space bar from 3x2.25U to 1x6.25U
2026-04-13 New reference scans for XE caps
2026-04-19 Parametric art frame
2026-04-19 H2C thin poop chute system
2026-04-19 MX caps models
2026-04-19 Accurate XE key caps with MX footprints
    Some XE glyph work
2026-04-19 Preliminary XE case work
2026-04-19 Update readmes
2026-06-08 ThockFactory caps design files for XE, XL, 1200XL and 800
